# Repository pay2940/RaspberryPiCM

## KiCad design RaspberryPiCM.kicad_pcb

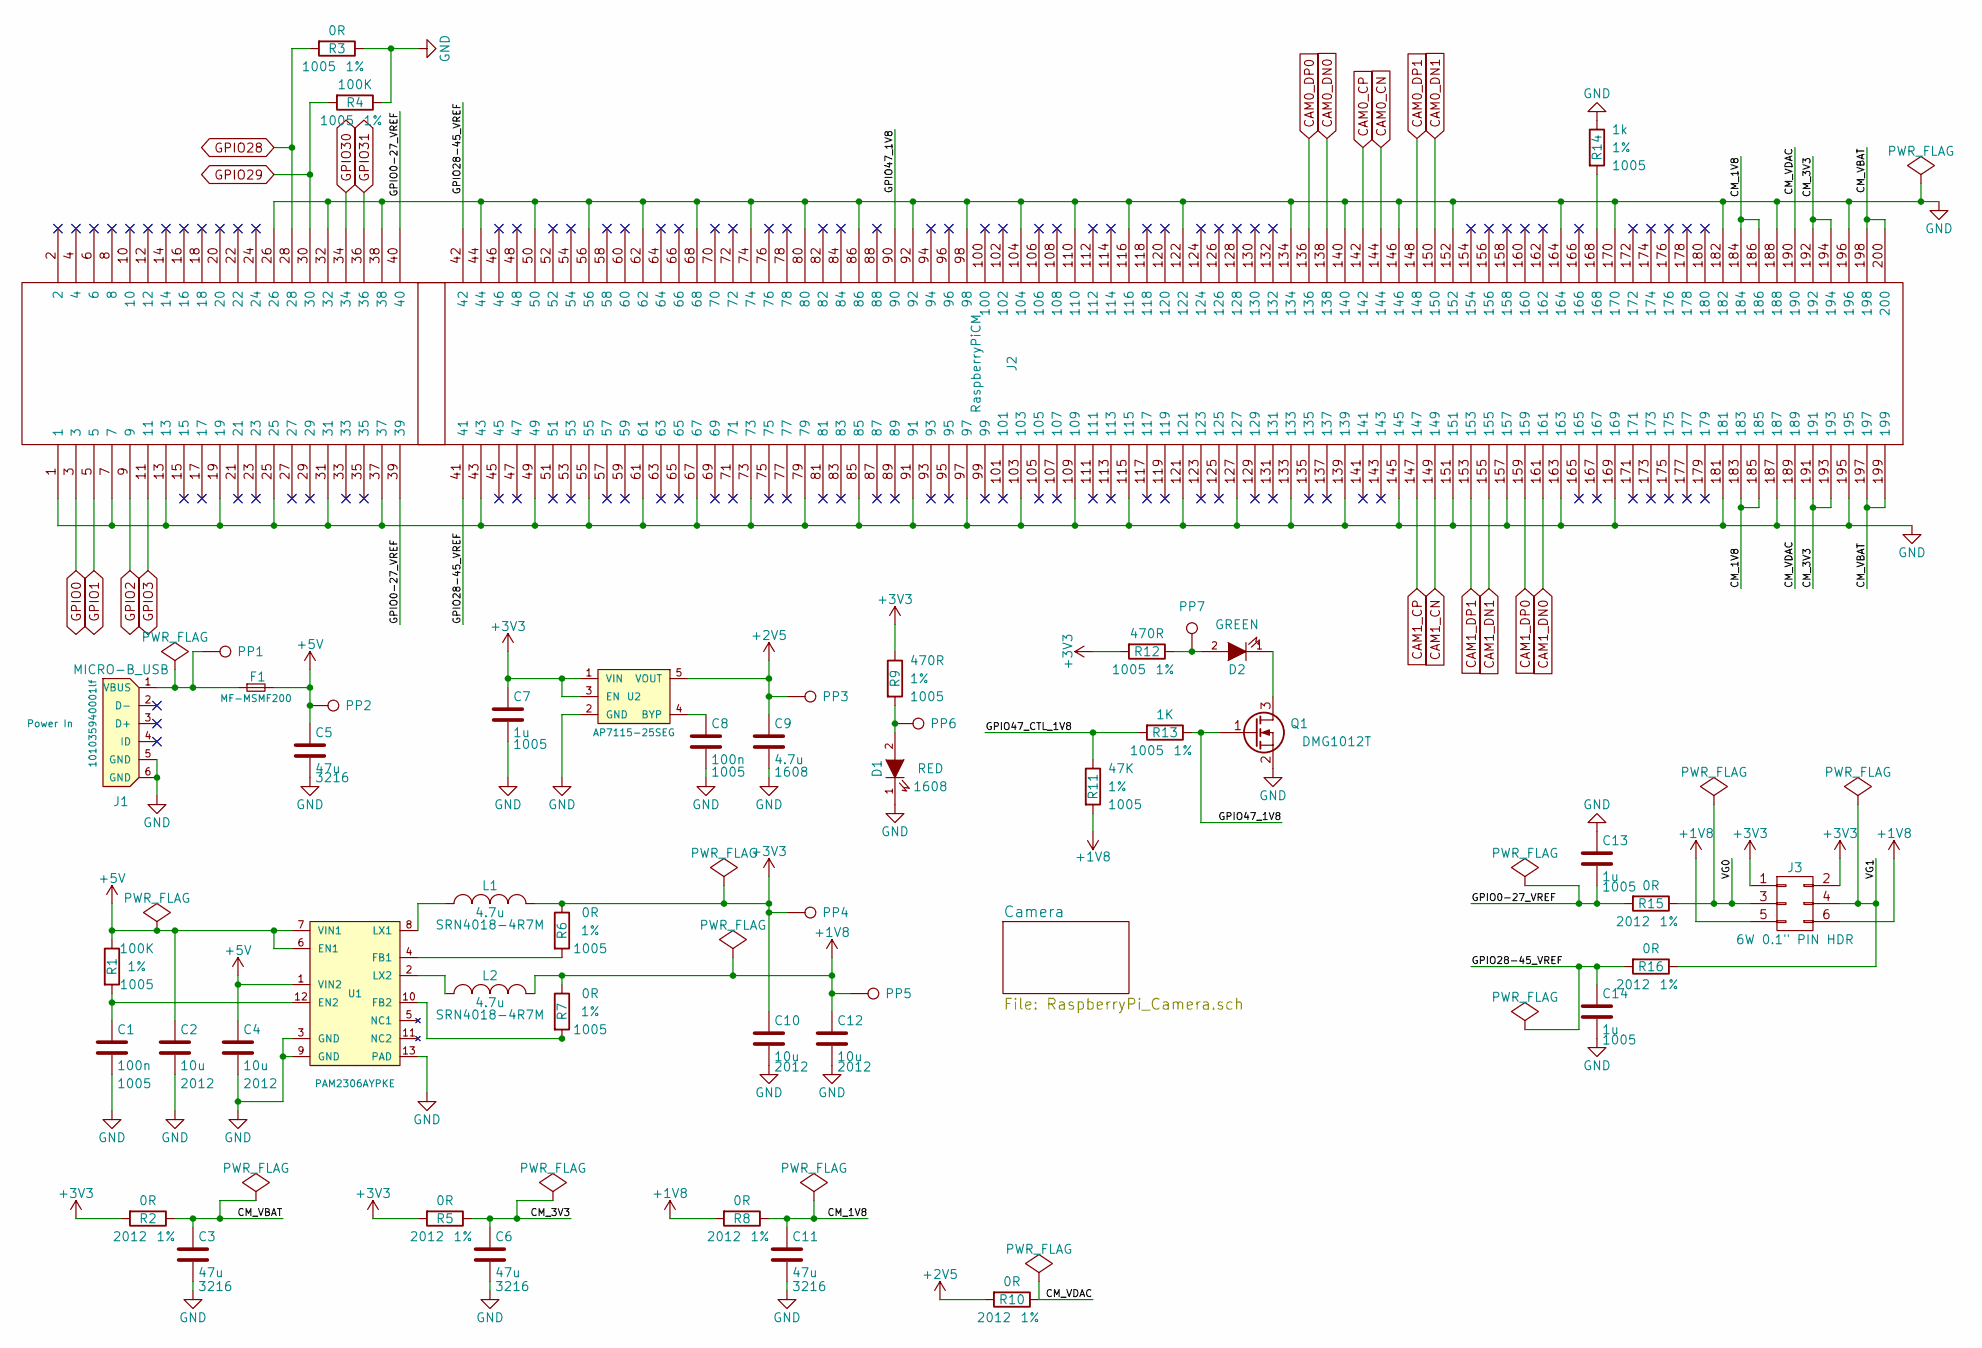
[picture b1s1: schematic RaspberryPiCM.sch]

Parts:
C1, C8: 100n; C_0402
C2, C4, C10, C12: 10u; C_0805
C3, C5, C6, C11: 47u; C_1206
C7, C13, C14: 1u; C_0402
C9: 4.7u; C_0603
D1: RED; LED-0603
D2: GREEN; LED-0603
F1: MF-MSMF200; MF-MSMFS200
J1: MICRO-B_USB; USB_Micro-B
J2: RaspberryPiCM; Socket_SODIMM_DDR1-2_TE_1612618
J3: 6W 0.1\" PIN HDR; Pin_Header_Straight_2x03
L1, L2: 4.7u; BOURNS-SRN4018-INDUCTOR
PP1, PP2, PP3, PP4, PP5, PP6, PP7: TEST_1P; PINTST
Q1: DMG1012T; SOT-523
R1, R4: 100K; R_0402
R2, R5, R8, R10, R15, R16: 0R; R_0805
R3, R6, R7: 0R; R_0402
R9, R12: 470R; R_0402
R11: 47K; R_0402
R13: 1K; R_0402
R14: 1k; R_0402
U1: PAM2306AYPKE; PAM2306
U2: AP7115-25SEG; SOT-353

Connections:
+1V8: C12.1, J3.5, J3.6, L2.2, PP5.1, R7.1, R8.2, R11.2
+2V5: C9.1, PP3.1, R10.2, U2.5 (VOUT)
+3V3: C7.1, C10.1, J3.1, J3.2, L1.2, PP4.1, R2.2, R5.2, R6.1, R9.1, R12.2, U2.1 (VIN), U2.3 (EN); also elsewhere on the board
+5V: C2.1, C4.1, C5.1, F1.2, PP2.1, R1.1, U1.1 (VIN2), U1.6 (EN1), U1.7 (VIN1)
/CM_1V8: C11.1, J2.183, J2.184, J2.185, J2.186, R8.1
/CM_3V3: C6.1, J2.191, J2.192, J2.193, J2.194, R5.1
/CM_VBAT: C3.1, J2.197, J2.198, J2.199, J2.200, R2.1
/CM_VDAC: J2.189, J2.190, R10.1
/GPIO0-27_VREF: C13.2, J2.39, J2.40, R15.2
/GPIO28-45_VREF: C14.1, J2.41, J2.42, R16.2
/GPIO47_1V8: J2.90, Q1.1 (G), R13.1
/GPIO47_CTL_1V8: R11.1, R13.2
/VG0: J3.3, R15.1
/VG1: J3.4, R16.1
CAM0_CN: J2.144; also elsewhere on the board
CAM0_CP: J2.142; also elsewhere on the board
CAM0_DN0: J2.138; also elsewhere on the board
CAM0_DN1: J2.150; also elsewhere on the board
CAM0_DP0: J2.136; also elsewhere on the board
CAM0_DP1: J2.148; also elsewhere on the board
CAM0_IO0: J2.36; also elsewhere on the board
CAM0_IO1: J2.34; also elsewhere on the board
CAM1_CN: J2.149; also elsewhere on the board
CAM1_CP: J2.147; also elsewhere on the board
CAM1_DN0: J2.161; also elsewhere on the board
CAM1_DN1: J2.155; also elsewhere on the board
CAM1_DP0: J2.159; also elsewhere on the board
CAM1_DP1: J2.153; also elsewhere on the board
CAM1_IO0: J2.11; also elsewhere on the board
CAM1_IO1: J2.9; also elsewhere on the board
CD0_SCL: J2.30, R4.2; also elsewhere on the board
CD0_SDA: J2.28, R3.2; also elsewhere on the board
CD1_SCL: J2.5; also elsewhere on the board
CD1_SDA: J2.3; also elsewhere on the board
GND: C1.2, C2.2, C3.2, C4.2, C5.2, C6.2, C7.2, C8.2, C9.2, C10.2, C11.2, C12.2, C13.1, C14.2, D1.1 (K), J1.5 (GND), J1.6 (GND), J2.1, J2.7, J2.13, J2.19, J2.25, J2.26, J2.31, J2.32, J2.37, J2.38, J2.43, J2.44, J2.49, J2.50, J2.55, J2.56, J2.61, J2.62, J2.67, J2.68, J2.73, J2.74, J2.79, J2.80, J2.85, J2.86, J2.91, J2.92, J2.97, J2.98, J2.103, J2.104, J2.109, J2.110, J2.115, J2.116, J2.121, J2.122, J2.127, J2.133, J2.134, J2.139, J2.140, J2.145, J2.146, J2.151, J2.152, J2.157, J2.163, J2.164, J2.169, J2.170, J2.181, J2.182, J2.187, J2.188, J2.195, J2.196, Q1.2 (S), R3.1, R4.1, R14.1, U1.3 (GND), U1.9 (GND), U1.13 (PAD), U2.2 (GND); also elsewhere on the board
unnamed: C1.1, R1.2, U1.12 (EN2)
unnamed: C8.1, U2.4 (BYP)
unnamed: D1.2 (A), PP6.1, R9.2
unnamed: D2.1 (K), Q1.3 (D)
unnamed: D2.2 (A), PP7.1, R12.1
unnamed: F1.1, J1.1 (VBUS), PP1.1
unnamed: J2.168, R14.2
unnamed: L1.1, U1.8 (LX1)
unnamed: L2.1, U1.2 (LX2)
unnamed: R6.2, U1.4 (FB1)
unnamed: R7.2, U1.10 (FB2)

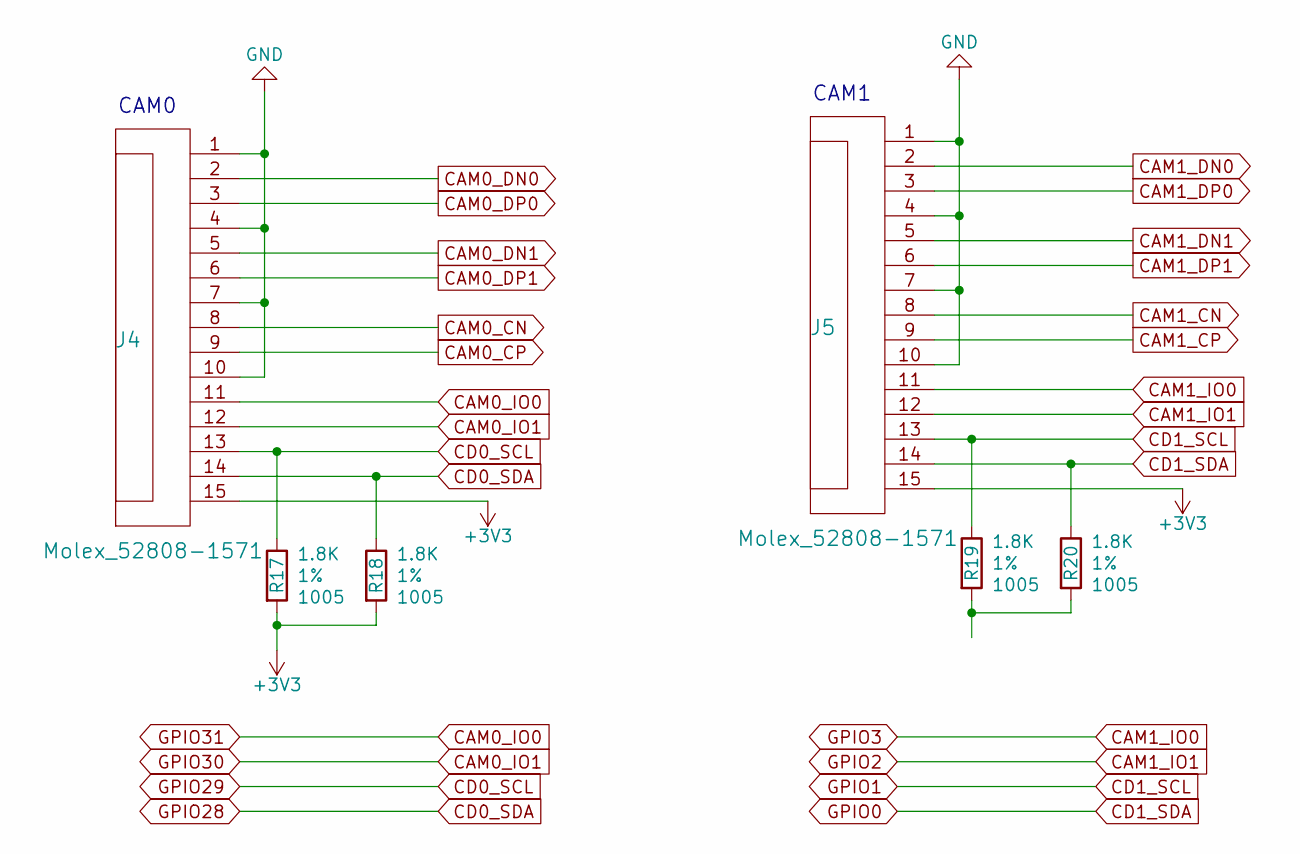
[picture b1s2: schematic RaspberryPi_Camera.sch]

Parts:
J4, J5: Molex_52808-1571; CONN-MOLEX-52808-1571
R17, R18, R19, R20: 1.8K; R_0402

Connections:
+3V3: J4.15, J5.15, R17.2, R18.2; also elsewhere on the board
CAM0_CN: J4.8; also elsewhere on the board
CAM0_CP: J4.9; also elsewhere on the board
CAM0_DN0: J4.2; also elsewhere on the board
CAM0_DN1: J4.5; also elsewhere on the board
CAM0_DP0: J4.3; also elsewhere on the board
CAM0_DP1: J4.6; also elsewhere on the board
CAM0_IO0: J4.11; also elsewhere on the board
CAM0_IO1: J4.12; also elsewhere on the board
CAM1_CN: J5.8; also elsewhere on the board
CAM1_CP: J5.9; also elsewhere on the board
CAM1_DN0: J5.2; also elsewhere on the board
CAM1_DN1: J5.5; also elsewhere on the board
CAM1_DP0: J5.3; also elsewhere on the board
CAM1_DP1: J5.6; also elsewhere on the board
CAM1_IO0: J5.11; also elsewhere on the board
CAM1_IO1: J5.12; also elsewhere on the board
CD0_SCL: J4.13, R17.1; also elsewhere on the board
CD0_SDA: J4.14, R18.1; also elsewhere on the board
CD1_SCL: J5.13, R19.1; also elsewhere on the board
CD1_SDA: J5.14, R20.1; also elsewhere on the board
GND: J4.1, J4.4, J4.7, J4.10, J5.1, J5.4, J5.7, J5.10; also elsewhere on the board
unnamed: R19.2, R20.2

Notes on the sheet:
CAM0
CAM1

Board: 2 copper layers, 54 parts (0 on the bottom side), 47 nets, no tracks yet.

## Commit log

2019-05-15 uploaded from gitlab
